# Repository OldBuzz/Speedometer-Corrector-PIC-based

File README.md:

# Speedometer-Corrector-PIC-based
Digital speedometer corrector, based on a PIC 18F1320.

This is a Microchip PIC 18F1320 project for correcting a speedometer when you change tire size or differential gearing. It was initially designed for a Jeep Wrangler TJ (1997-2006). It may also work on other vehicles if they use a 5 volt squarewave signal from the speed sensor to the speedometer or to the PCM/ECU, within the range of 0 Hz to a little over 200 Hz. Some vehicles use a 12 volt speedometer signal, which would require several changes to this circuit to work. Some vehicles may use other signals, like a sinewave, or a CAN bus serial stream. This circuit will not work for those vehicles.

## Important Note

Installing this device involves splicing into your vehicle wiring, and altering the way a sensor reports to the PCM/ECU (engine computer). If you're uncomfortable with doing that, don't. An error could be very costly. It also requires you to burn a program into a PIC microcontroller. If you don't have the equipment to do that, it will cost money and a learning curve to get set up. It's probably not worth it unless you're going to play with other PIC microcontrollers for your own projects. On the other hand, the circuit is simple, with common through-hole parts, and the firmware is short and clean. Calibration is pretty easy.

## How It Works

The Speedo Corrector is a small box which goes between the Vehicle Speed Sensor on your transmission or transfer case and your engine computer (PCM/ECU). It alters the signal to correct for a change in tire diameter or gearing.

First, you take a drive to compare the indicated speed on your speedometer with a GPS speed. You'll do a simple calculation to get a "correction factor", which you'll enter into the Speedo Corrector on a set of 8 switches.

The Speedo Corrector measures the period of the incoming squarewave from the speed sensor, and produces a longer or shorter output squarewave, depending on the correction factor you set.

## License

The firmware is released as Open Source software.
Firmware License: GPL v3

The hardware is released as Open Hardware.
Hardware License: CERN-OHL-S v2

## Hardware

This simple circuit uses common through-hole parts. You can build it on a sea-of-holes proto board, wiring it point-to-point. Or you can make a real PC board, and the KiCad schematic and PCB layout, with Gerber files, is included.

## Firmware

The firmware is pretty short, and is written in C. You'll need the equipment to burn the firmware into the PIC chip.  Microchip MPLAB X IDE v6.20 (free), Microchip XC8 v3.00 compiler (free), Microchip PICkit3 or 4 (costs money) or equivalent.

## Where can I get one?

You'll have to acquire the parts and build it yourself.

## Related Projects

Speedometer Corrector (Arduino-based): An Arduino Pro Mini based speedometer corrector circuit.

https://github.com/OldBuzz/Speedometer-Corrector-Arduino-based

(I previously built an Arduino-based speedometer corrector, based on Tom M'Guinness's design. It works well, and I ran it in my Jeep for over two years.)

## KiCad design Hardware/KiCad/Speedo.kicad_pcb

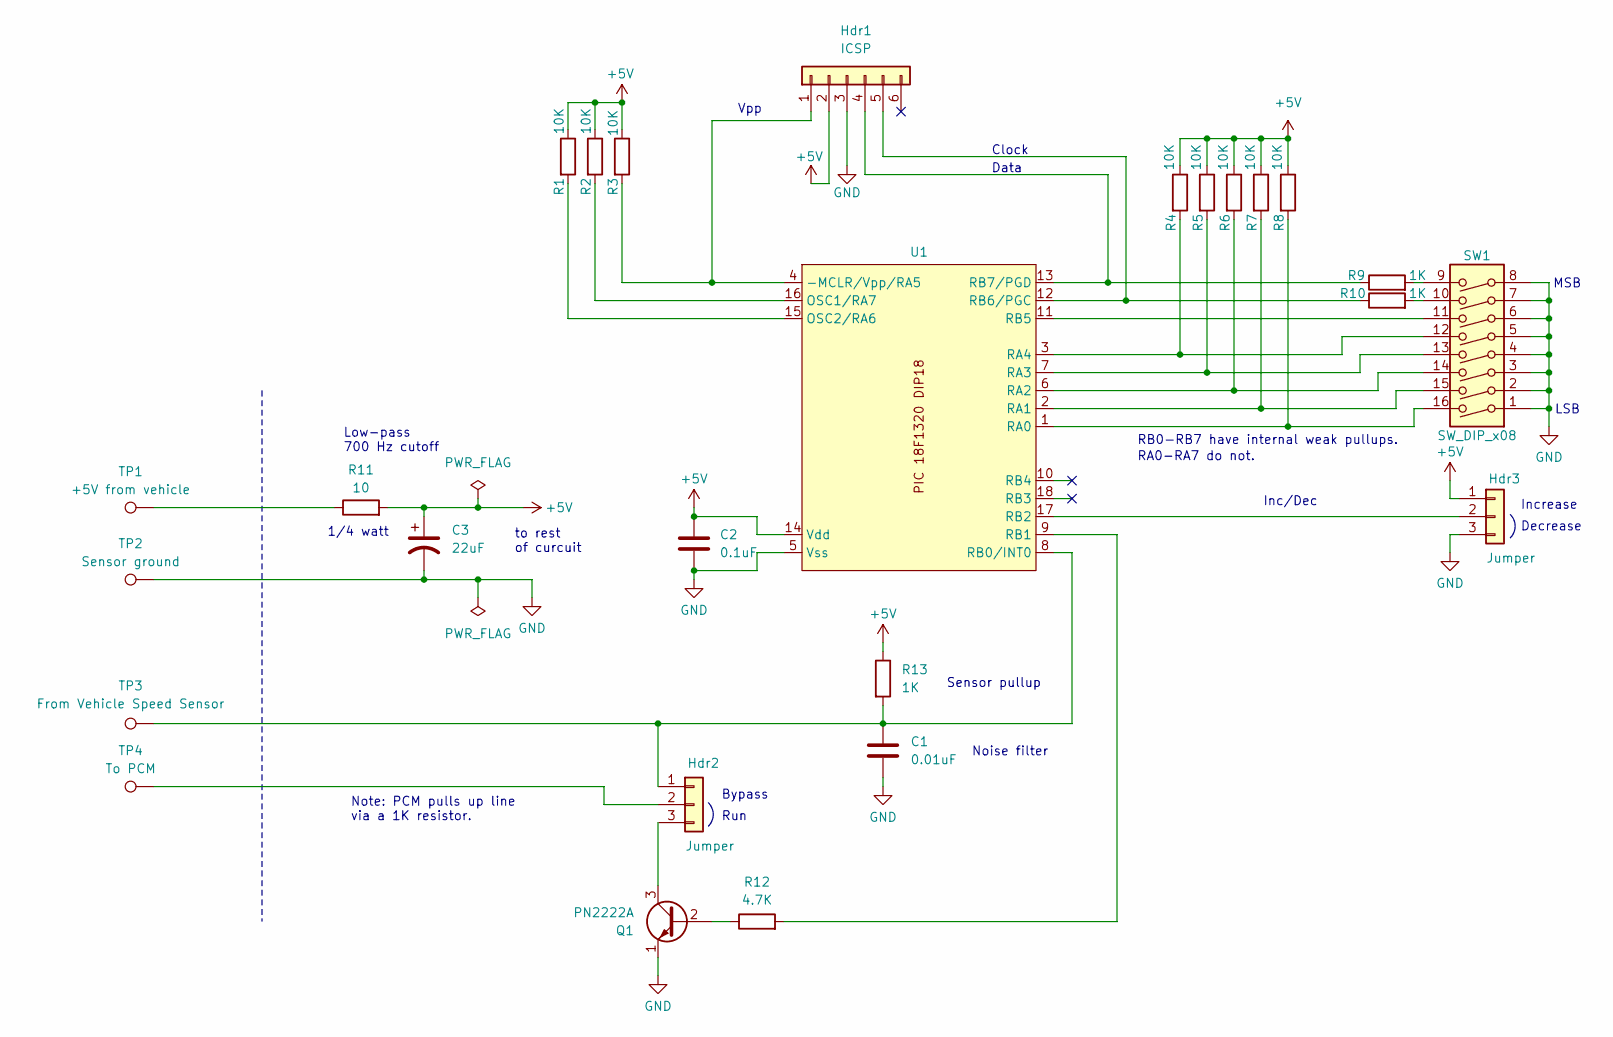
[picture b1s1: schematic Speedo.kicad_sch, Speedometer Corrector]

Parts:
C1: 0.01uF; C_Disc_D6.0mm_W2.5mm_P5.00mm
C2: 0.1uF; C_Disc_D3.0mm_W1.6mm_P2.50mm
C3: 22uF; CP_Radial_D6.3mm_P2.50mm
Hdr1: ICSP; PinHeader_1x06_P2.54mm_Vertical
Hdr2, Hdr3: Jumper; PinHeader_1x03_P2.54mm_Vertical
Q1: PN2222A; TO-92_Inline
R1, R2, R3, R4, R5, R6, R7, R8: 10K; R_Axial_DIN0207_L6.3mm_D2.5mm_P2.54mm_Vertical
R9, R10, R13: 1K; R_Axial_DIN0207_L6.3mm_D2.5mm_P2.54mm_Vertical
R11: 10; R_Axial_DIN0207_L6.3mm_D2.5mm_P2.54mm_Vertical
R12: 4.7K; R_Axial_DIN0207_L6.3mm_D2.5mm_P10.16mm_Horizontal
SW1: SW_DIP_x08; SW_DIP_SPSTx08_Slide_9.78x22.5mm_W7.62mm_P2.54mm
TP1: +5V from vehicle; TestPoint_THTPad_D3.0mm_Drill1.5mm
TP2: Sensor ground; TestPoint_THTPad_D3.0mm_Drill1.5mm
TP3: From Vehicle Speed Sensor; TestPoint_THTPad_D3.0mm_Drill1.5mm
TP4: To PCM; TestPoint_THTPad_D3.0mm_Drill1.5mm
U1: DIP-18_W7.62mm_LongPads

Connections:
+5V: C2.1, C3.1, Hdr1.2, Hdr3.1, R1.1, R2.1, R3.1, R4.1, R5.1, R6.1, R7.1, R8.1, R11.2, R13.1, U1.14 (Vdd)
GND: C1.2, C2.2, C3.2, Hdr1.3, Hdr3.3, Q1.1 (E), SW1.1, SW1.2, SW1.3, SW1.4, SW1.5, SW1.6, SW1.7, SW1.8, TP2.1, U1.5 (Vss)
unnamed: Hdr1.1, R3.2, U1.4 (-MCLR/Vpp/RA5)
unnamed: Hdr1.4, R9.1, U1.13 (RB7/PGD)
unnamed: Hdr1.5, R10.1, U1.12 (RB6/PGC)
unnamed: C1.1, Hdr2.1, R13.2, TP3.1, U1.8 (RB0/INT0)
unnamed: Hdr2.2, TP4.1
unnamed: Hdr2.3, Q1.3 (C)
unnamed: Hdr3.2, U1.17 (RB2)
unnamed: Q1.2 (B), R12.1
unnamed: R9.2, SW1.9
unnamed: R10.2, SW1.10
unnamed: R11.1, TP1.1
unnamed: R2.2, U1.16 (OSC1/RA7)
unnamed: R1.2, U1.15 (OSC2/RA6)
unnamed: R8.2, SW1.16, U1.1 (RA0)
unnamed: R7.2, SW1.15, U1.2 (RA1)
unnamed: R6.2, SW1.14, U1.6 (RA2)
unnamed: R5.2, SW1.13, U1.7 (RA3)
unnamed: R4.2, SW1.12, U1.3 (RA4)
unnamed: R12.2, U1.9 (RB1)
unnamed: SW1.11, U1.11 (RB5)

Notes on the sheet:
1/4 watt
Increase
Bypass
Decrease
RB0-RB7 have internal weak pullups.
Clock
Noise filter
to rest of curcuit
Sensor pullup
Run
MSB
RA0-RA7 do not.
Vpp
Low-pass 700 Hz cutoff
Data
LSB
Inc/Dec
Note: PCM pulls up line via a 1K resistor.

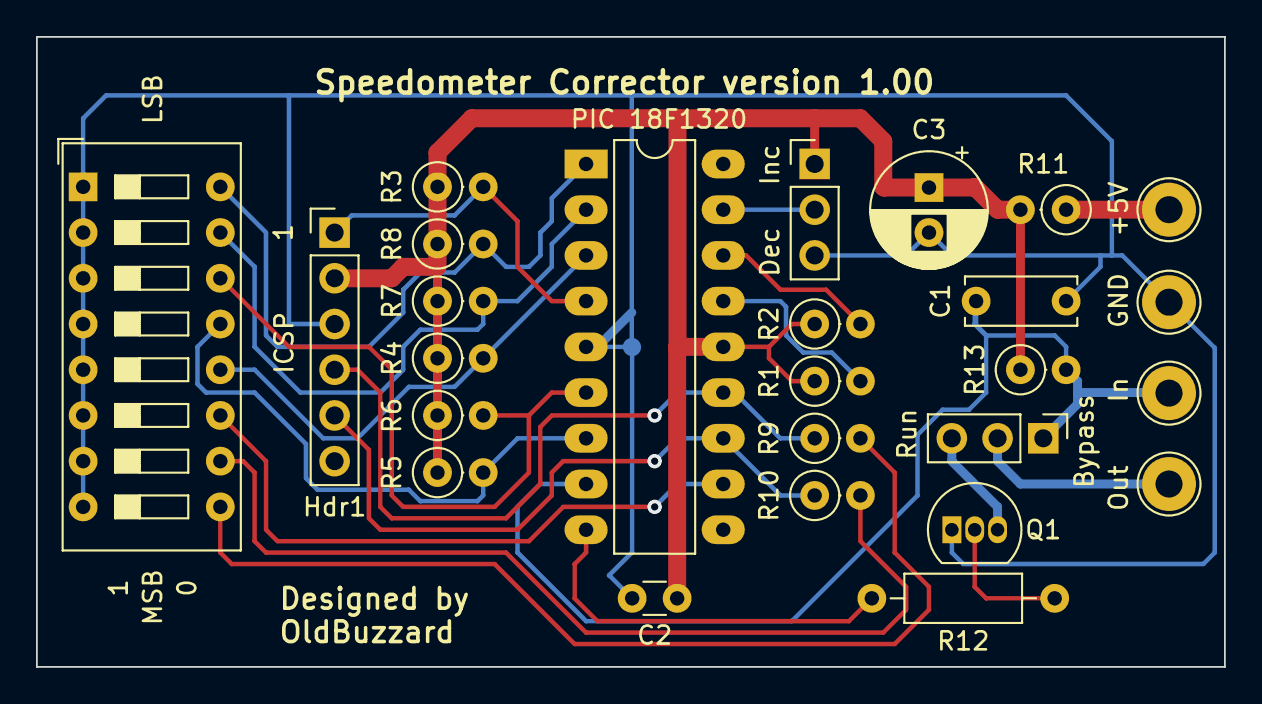
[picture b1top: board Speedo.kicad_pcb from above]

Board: 2 copper layers, 66.0 x 35.0 mm, 26 parts (0 on the bottom side), 22 nets.

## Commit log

2025-08-10 Rename Speedo_Corrector_Builting_It.txt to Speedo_Corrector_Building_It.txt

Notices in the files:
Hardware/KiCad/Speedo.kicad_pcb:
Copyright 2025 Dale A. Keller (OldBuzzard), Licensed under CERN-OHL-S version 2.
